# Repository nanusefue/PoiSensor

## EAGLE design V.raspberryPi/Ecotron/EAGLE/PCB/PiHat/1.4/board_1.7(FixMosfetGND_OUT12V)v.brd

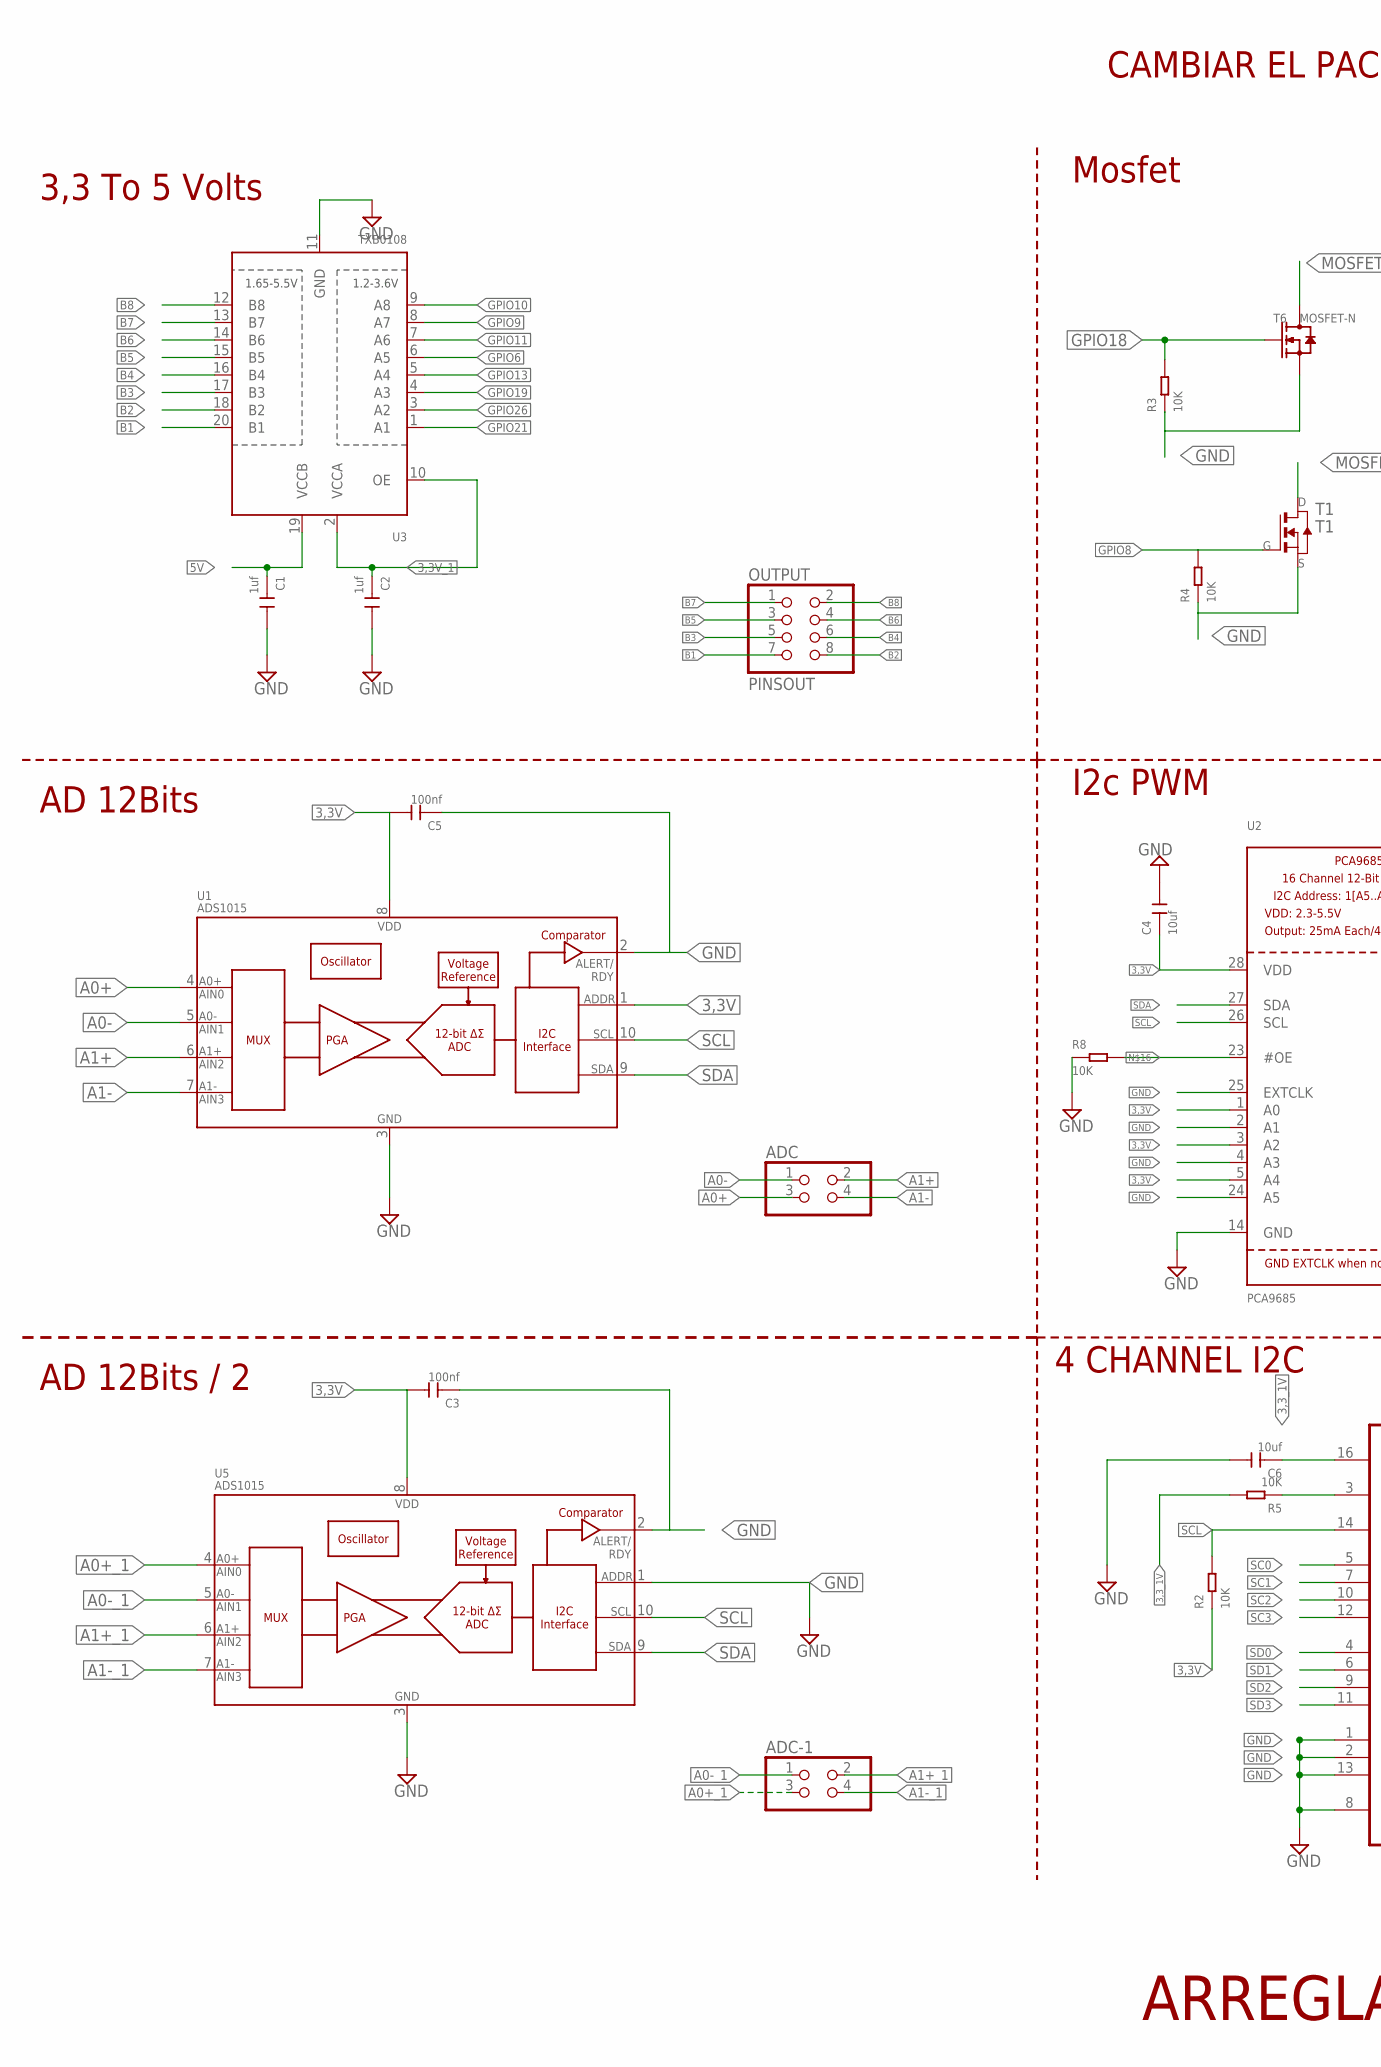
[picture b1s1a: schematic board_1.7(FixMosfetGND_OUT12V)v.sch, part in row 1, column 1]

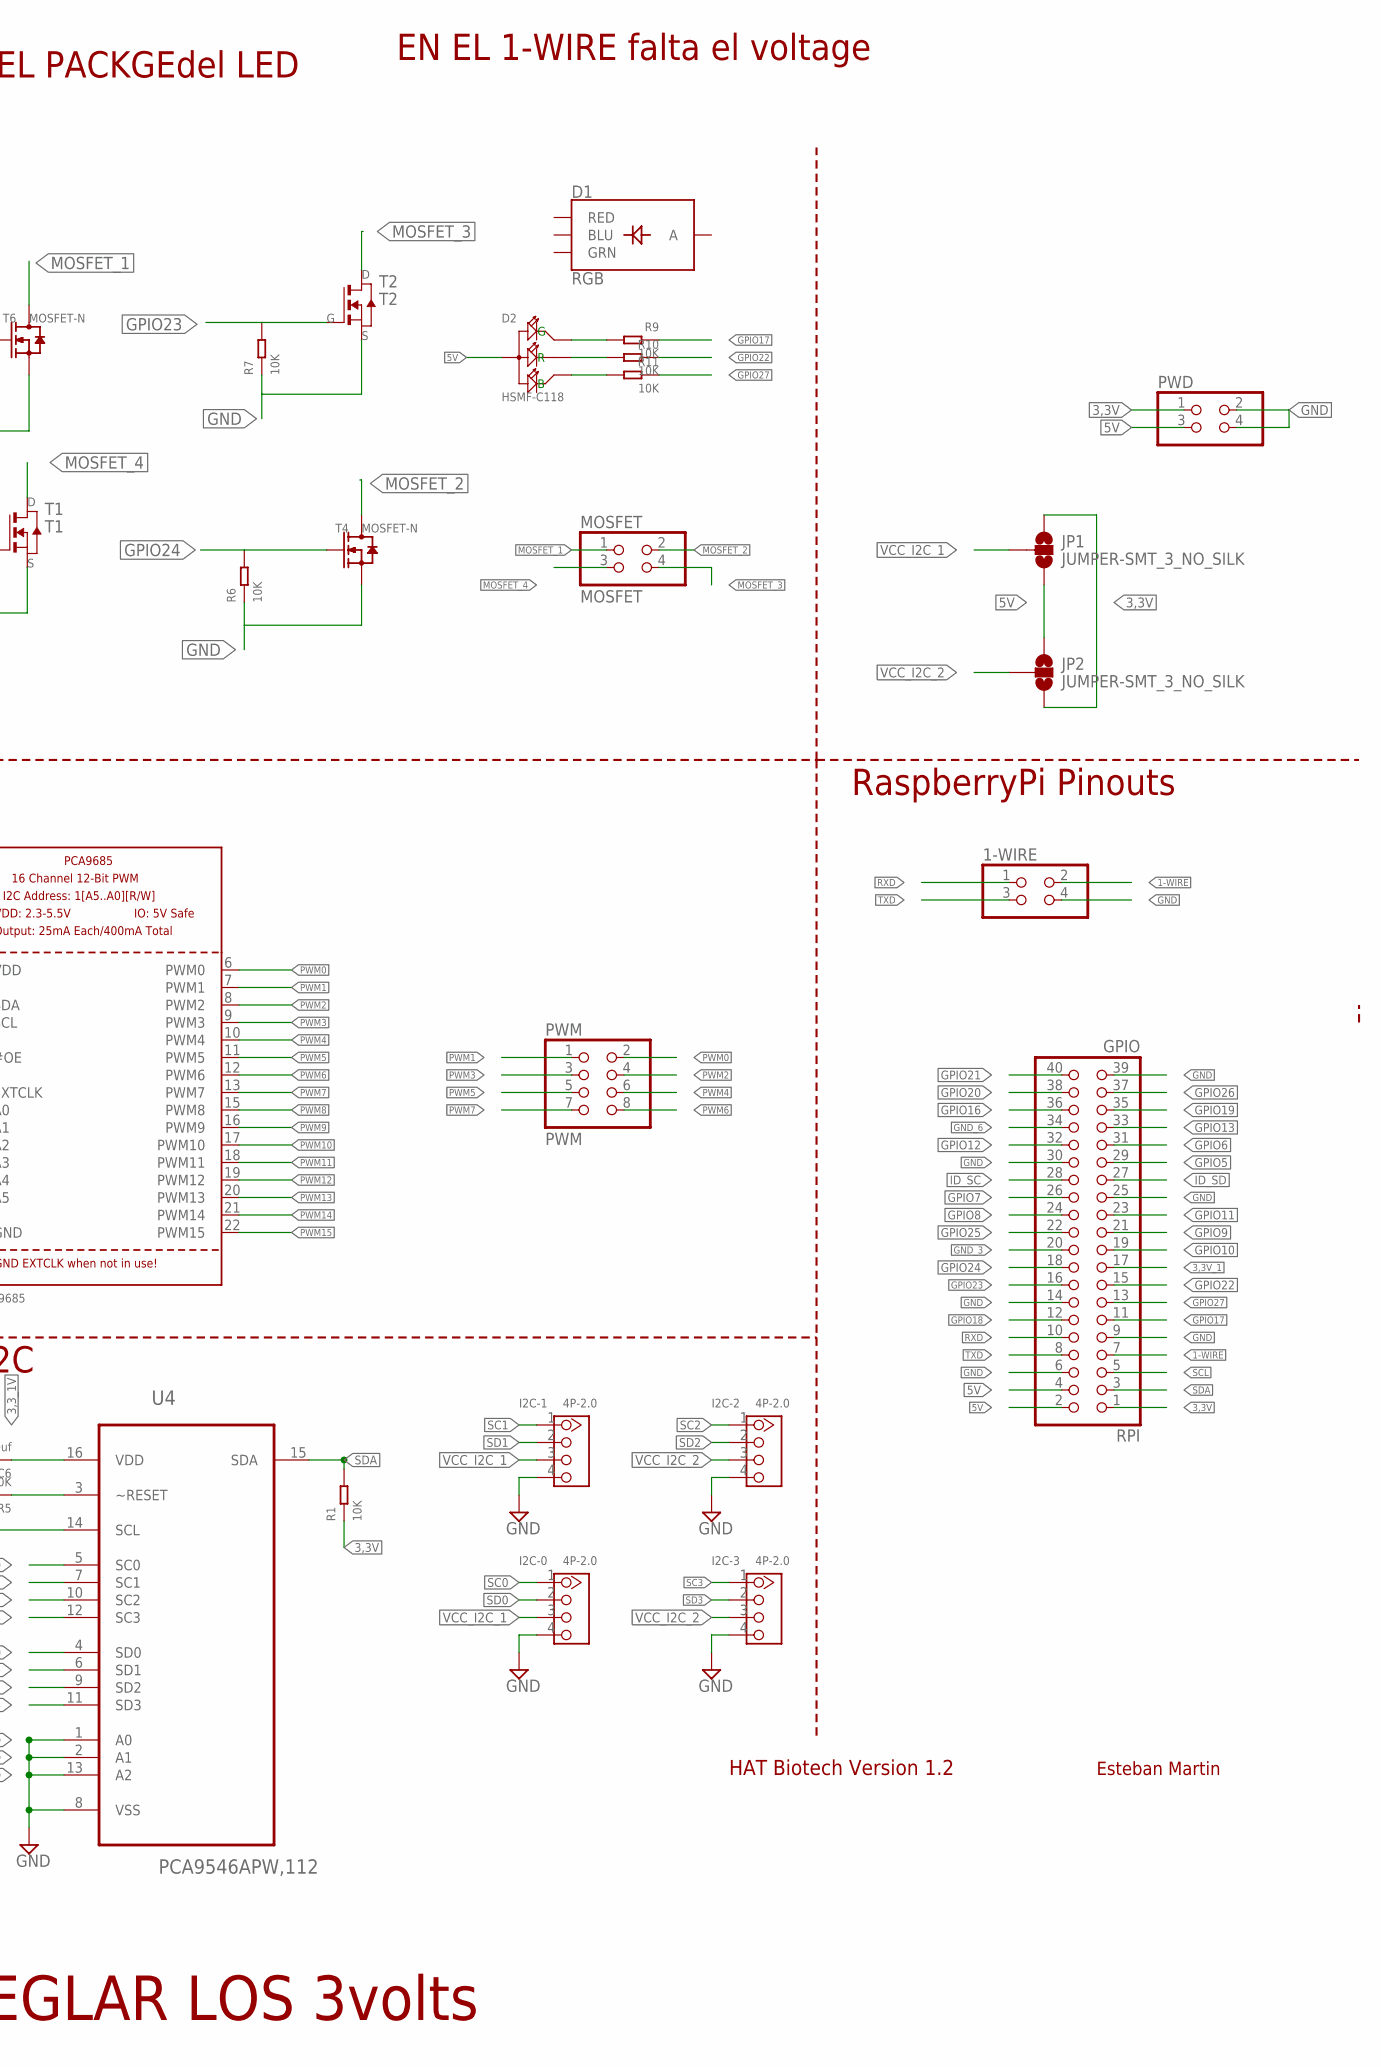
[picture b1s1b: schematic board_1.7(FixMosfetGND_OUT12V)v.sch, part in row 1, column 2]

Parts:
1-WIRE: PINHD-2X2; 2X02
ADC: PINHD-2X2; 2X02
ADC-1: PINHD-2X2; 2X02
C1, C2: 1uf; C0805
C3, C5: 100nf; C0805
C4, C6: 10uf; C0805
D1: RGB; P-LCC-4-3
D2: HSMF-C118; LED4-SMD-1210
I2C-0, I2C-1, I2C-2, I2C-3: 4P-2.0; HW4-2.0
JP1, JP2: JUMPER-SMT_3_NO_SILK; SMT-JUMPER_3_NO_SILK
MOSFET: MOSFET; 2X02
OUTPUT: PINSOUT; 2X04
PWD: PINHD-2X2; 2X02
PWM: PWM; 2X04
R1, R2, R3, R4, R5, R6, R7, R8, R9, R10, R11: 10K; R0805
RPI: GPIO; 2X20
T1: T1; TO252
T2: T2; TO252
T4, T6: MOSFET-N; SOT-23
U1, U5: ADS1015; MSOP10
U2: PCA9685; TSSOP28
U3: TXB0108; TSSOP20
U4: PCA9546APW,112; SOP65P640X110-16N

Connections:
1-WIRE: 1-WIRE.2, RPI.7
3,3V: C3.2, C4.1, C5.2, JP1.1, JP2.3, PWD.1, R1.1, R2.1, RPI.1, U1.1 (ADDR), U1.8 (VDD), U2.1 (A0), U2.3 (A2), U2.5 (A4), U2.28 (VDD), U5.8 (VDD)
3,3V_1: C2.1, RPI.17, U3.2 (VCCA), U3.10 (OE)
3,3_1V: C6.1, R5.2, U4.16 (VDD)
5V: C1.1, D2.1 (+), JP1.3, JP2.1, PWD.3, RPI.2, RPI.4, U3.19 (VCCB)
A0+: ADC.3, U1.4 (AIN0)
A0+_1: ADC-1.3, U5.4 (AIN0)
A0-: ADC.1, U1.5 (AIN1)
A0-_1: ADC-1.1, U5.5 (AIN1)
A1+: ADC.2, U1.6 (AIN2)
A1+_1: ADC-1.2, U5.6 (AIN2)
A1-: ADC.4, U1.7 (AIN3)
A1-_1: ADC-1.4, U5.7 (AIN3)
B1: OUTPUT.7, U3.20 (B1)
B2: OUTPUT.8, U3.18 (B2)
B3: OUTPUT.5, U3.17 (B3)
B4: OUTPUT.6, U3.16 (B4)
B5: OUTPUT.3, U3.15 (B5)
B6: OUTPUT.4, U3.14 (B6)
B7: OUTPUT.1, U3.13 (B7)
B8: OUTPUT.2, U3.12 (B8)
GND: 1-WIRE.4, C1.2, C2.2, C3.1, C4.2, C5.1, C6.2, I2C-0.4, I2C-1.4, I2C-2.4, I2C-3.4, PWD.2, PWD.4, R3.1, R4.1, R6.1, R7.1, R8.1, RPI.6, RPI.9, RPI.14, RPI.25, RPI.30, RPI.39, T1.2 (S), T2.2 (S), T4.2 (S), T6.2 (S), U1.2 (ALERT/RDY), U1.3 (VSS), U2.2 (A1), U2.4 (A3), U2.14 (GND), U2.24 (A5), U2.25 (EXTCLK), U3.11 (GND), U4.1 (A0), U4.2 (A1), U4.8 (VSS), U4.13 (A2), U5.1 (ADDR), U5.2 (ALERT/RDY), U5.3 (VSS)
GND_3: RPI.20
GND_6: RPI.34
GPIO5: RPI.29
GPIO6: RPI.31, U3.6 (A5)
GPIO7: RPI.26
GPIO8: R4.2, RPI.24, T1.1 (G)
GPIO9: RPI.21, U3.8 (A7)
GPIO10: RPI.19, U3.9 (A8)
GPIO11: RPI.23, U3.7 (A6)
GPIO12: RPI.32
GPIO13: RPI.33, U3.5 (A4)
GPIO16: RPI.36
GPIO17: R9.1, RPI.11
GPIO18: R3.2, RPI.12, T6.1 (G)
GPIO19: RPI.35, U3.4 (A3)
GPIO20: RPI.38
GPIO21: RPI.40, U3.1 (A1)
GPIO22: R10.1, RPI.15
GPIO23: R7.2, RPI.16, T2.1 (G)
GPIO24: R6.2, RPI.18, T4.1 (G)
GPIO25: RPI.22
GPIO26: RPI.37, U3.3 (A2)
GPIO27: R11.1, RPI.13
ID_SC: RPI.28
ID_SD: RPI.27
MOSFET_1: MOSFET.1, T6.3 (D)
MOSFET_2: MOSFET.2, T4.3 (D)
MOSFET_3: MOSFET.4, T2.3 (D)
MOSFET_4: MOSFET.3, T1.3 (D)
unnamed: D2.3 (G), R9.2
unnamed: D2.2 (R), R10.2
unnamed: D2.4 (B), R11.2
unnamed: R5.1, U4.3 (~RESET)
unnamed: R8.2, U2.23 (#OE)
PWM0: PWM.2, U2.6 (PWM0)
PWM1: PWM.1, U2.7 (PWM1)
PWM2: PWM.4, U2.8 (PWM2)
PWM3: PWM.3, U2.9 (PWM3)
PWM4: PWM.6, U2.10 (PWM4)
PWM5: PWM.5, U2.11 (PWM5)
PWM6: PWM.8, U2.12 (PWM6)
PWM7: PWM.7, U2.13 (PWM7)
PWM8: U2.15 (PWM8)
PWM9: U2.16 (PWM9)
PWM10: U2.17 (PWM10)
PWM11: U2.18 (PWM11)
PWM12: U2.19 (PWM12)
PWM13: U2.20 (PWM13)
PWM14: U2.21 (PWM14)
PWM15: U2.22 (PWM15)
RXD: 1-WIRE.1, RPI.10
SC0: I2C-0.1, U4.5 (SC0)
SC1: I2C-1.1, U4.7 (SC1)
SC2: I2C-2.1, U4.10 (SC2)
SC3: I2C-3.1, U4.12 (SC3)
SCL: R2.2, RPI.5, U1.10 (SCL), U2.26 (SCL), U4.14 (SCL), U5.10 (SCL)
SD0: I2C-0.2, U4.4 (SD0)
SD1: I2C-1.2, U4.6 (SD1)
SD2: I2C-2.2, U4.9 (SD2)
SD3: I2C-3.2, U4.11 (SD3)
SDA: R1.2, RPI.3, U1.9 (SDA), U2.27 (SDA), U4.15 (SDA), U5.9 (SDA)
TXD: 1-WIRE.3, RPI.8
VCC_I2C_1: I2C-0.3, I2C-1.3, JP1.2
VCC_I2C_2: I2C-2.3, I2C-3.3, JP2.2

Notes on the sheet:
AD 12Bits
3,3 To 5 Volts
Mosfet
RaspberryPi Pinouts
I2c PWM
HAT Biotech Version 1.2
Esteban Martin
4 CHANNEL I2C
AD 12Bits / 2
ARREGLAR LOS 3volts
CAMBIAR EL PACKGEdel LED
EN EL 1-WIRE falta el voltage

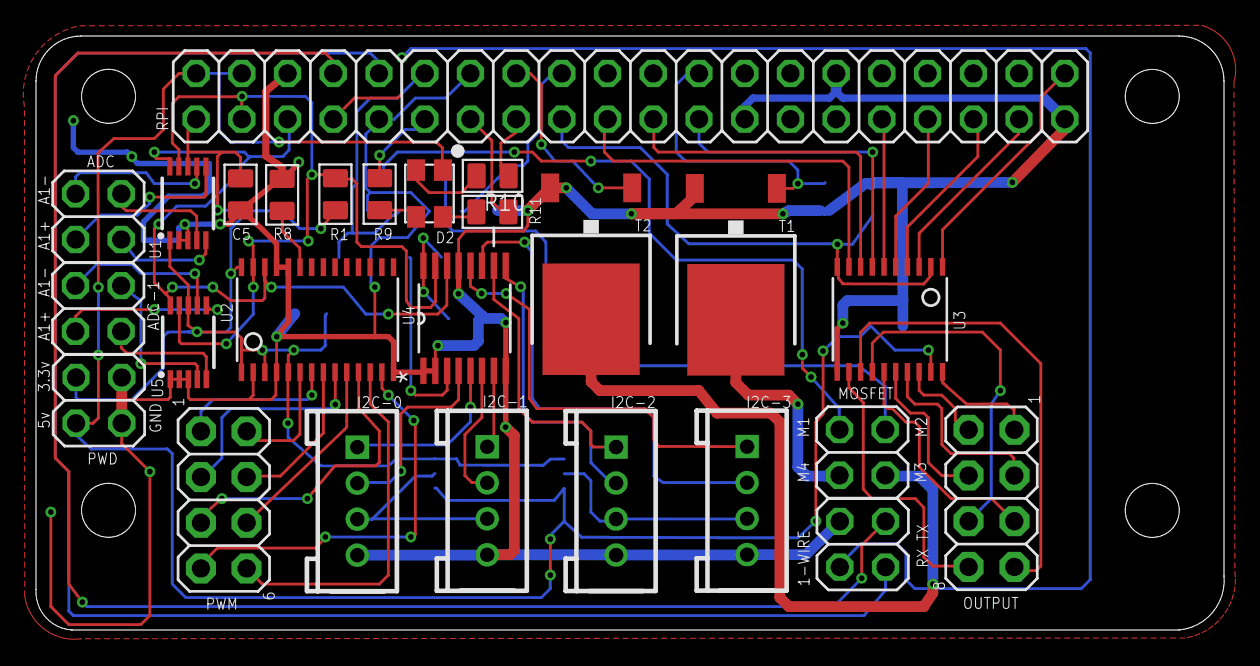
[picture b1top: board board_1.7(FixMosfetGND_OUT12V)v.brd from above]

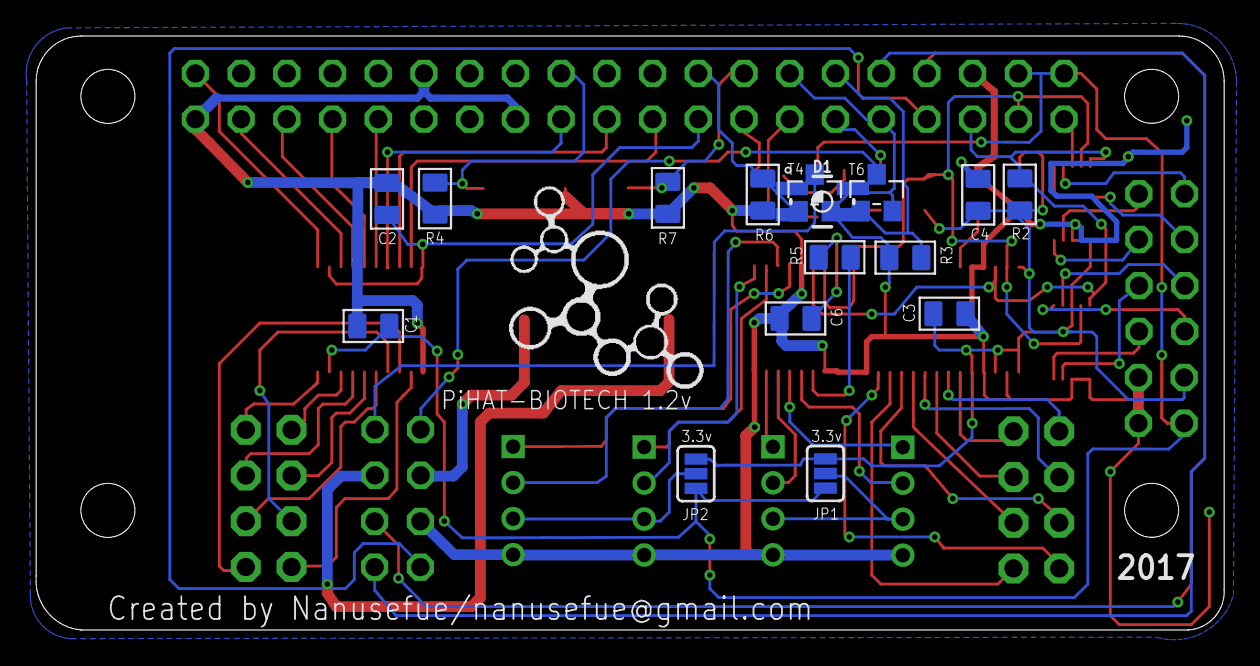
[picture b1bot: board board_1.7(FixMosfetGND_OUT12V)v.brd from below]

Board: 2 copper layers, 66.0 x 33.0 mm, 42 parts (16 on the bottom side), 68 nets.

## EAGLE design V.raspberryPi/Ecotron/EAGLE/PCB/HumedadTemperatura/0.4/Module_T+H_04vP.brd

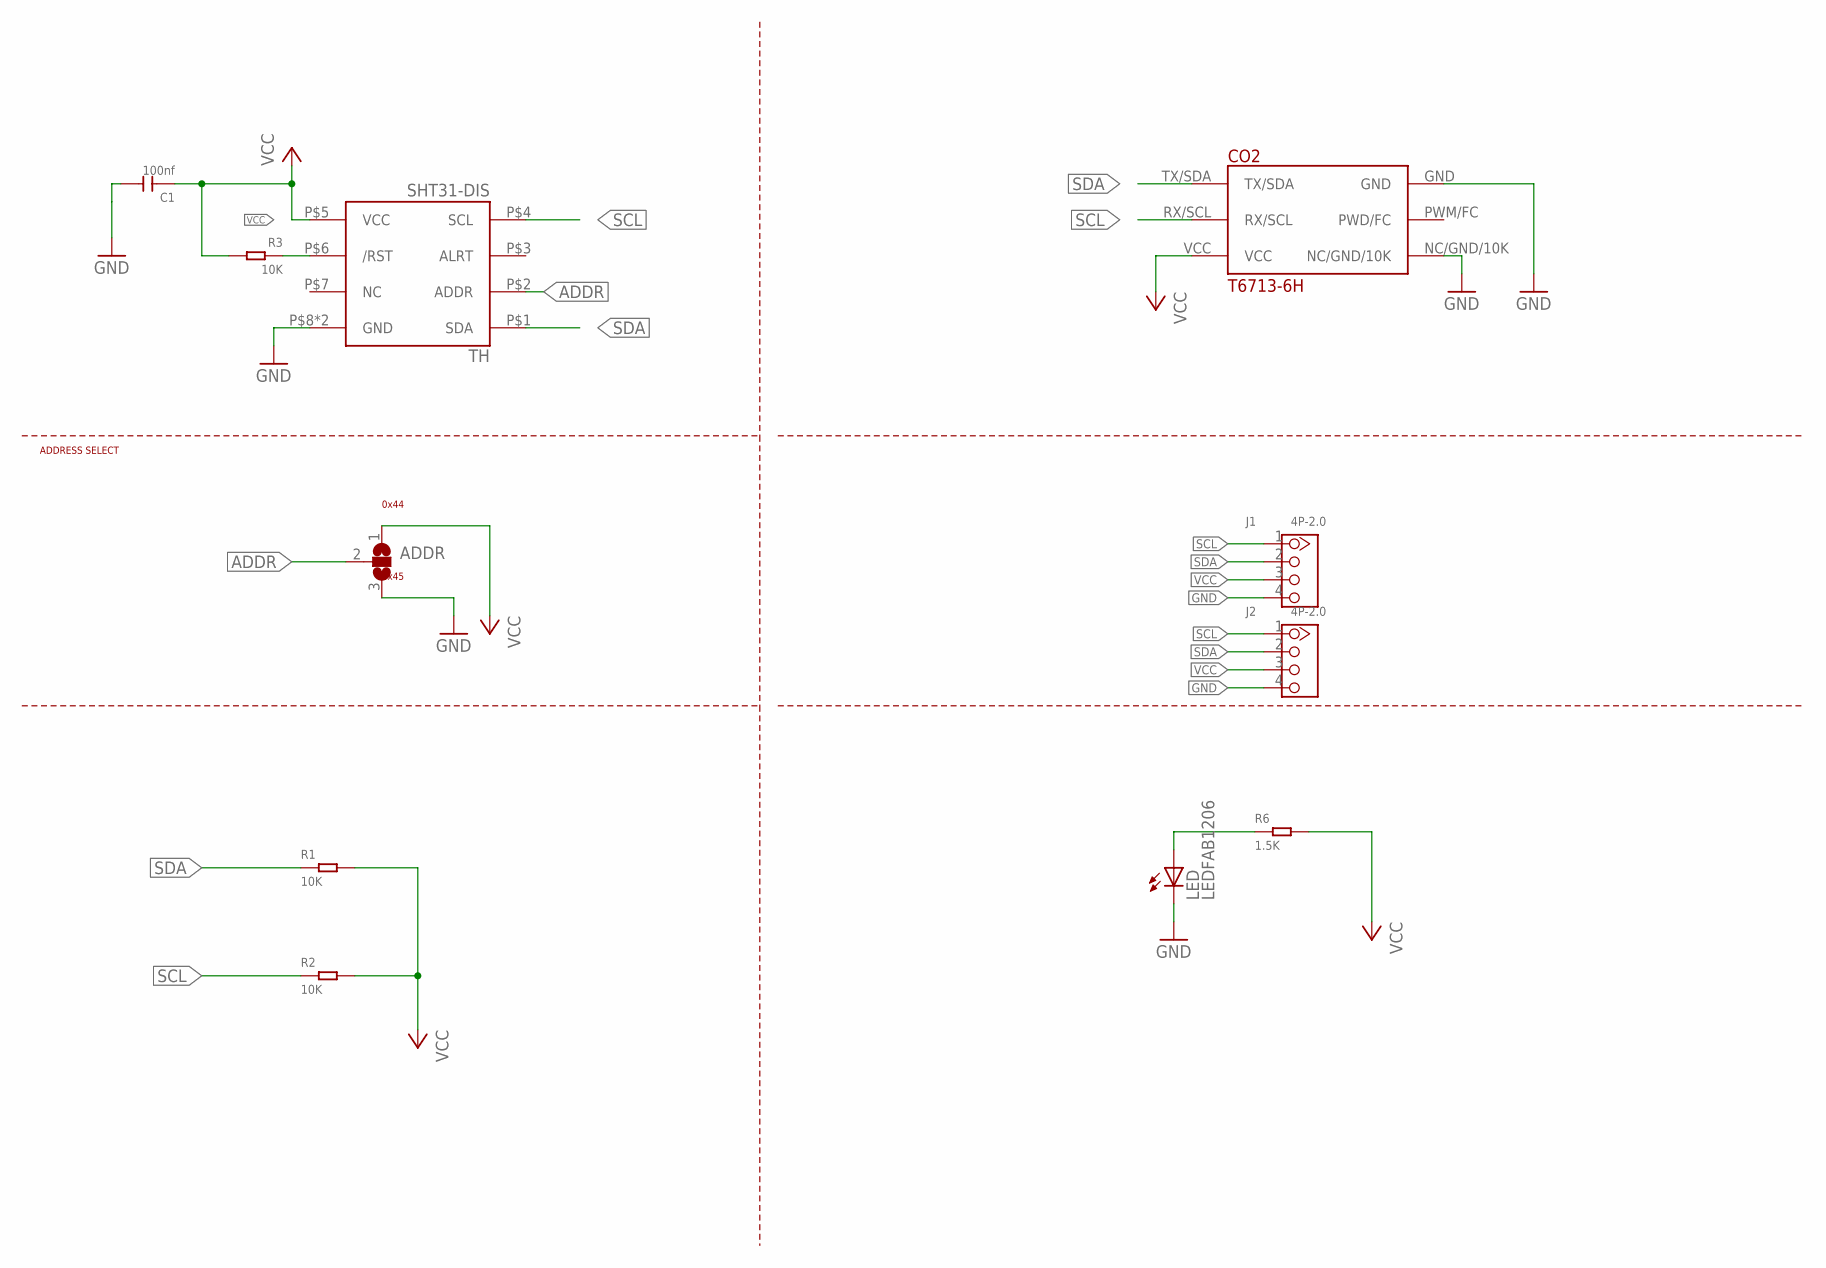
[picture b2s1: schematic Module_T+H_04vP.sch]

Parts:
ADDR: SJ2W; SJ_2
C1: 100nf; C0805
CO2: T6713-6H; PINS
J1, J2: 4P-2.0; HW4-2.0
LED: LEDFAB1206; LED1206FAB
R1, R2, R3: 10K; R0805
R6: 1.5K; R0805
TH: SHT31-DIS; SHT3X

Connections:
ADDR: ADDR.2, TH.P$2 (ADDR)
GND: ADDR.3, C1.2, CO2.GND, CO2.NC/GND/10K, J1.4, J2.4, LED.2 (C), TH.P$8 (GND), TH.PAD (GND)
unnamed: LED.1 (A), R6.1
RST: R3.1, TH.P$6 (/RST)
SCL: CO2.RX/SCL, J1.1, J2.1, R2.1, TH.P$4 (SCL)
SDA: CO2.TX/SDA, J1.2, J2.2, R1.1, TH.P$1 (SDA)
VCC: ADDR.1, C1.1, CO2.VCC, J1.3, J2.3, R1.2, R2.2, R3.2, R6.2, TH.P$5 (VCC)

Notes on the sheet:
ADDRESS SELECT
0x44
0x45

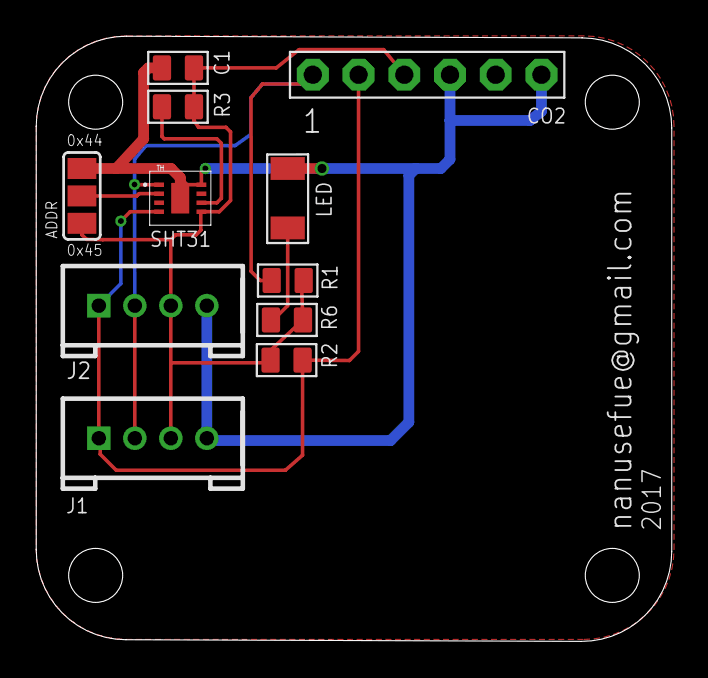
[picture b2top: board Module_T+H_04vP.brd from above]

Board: 2 copper layers, 35.3 x 33.6 mm, 11 parts (0 on the bottom side), 7 nets.

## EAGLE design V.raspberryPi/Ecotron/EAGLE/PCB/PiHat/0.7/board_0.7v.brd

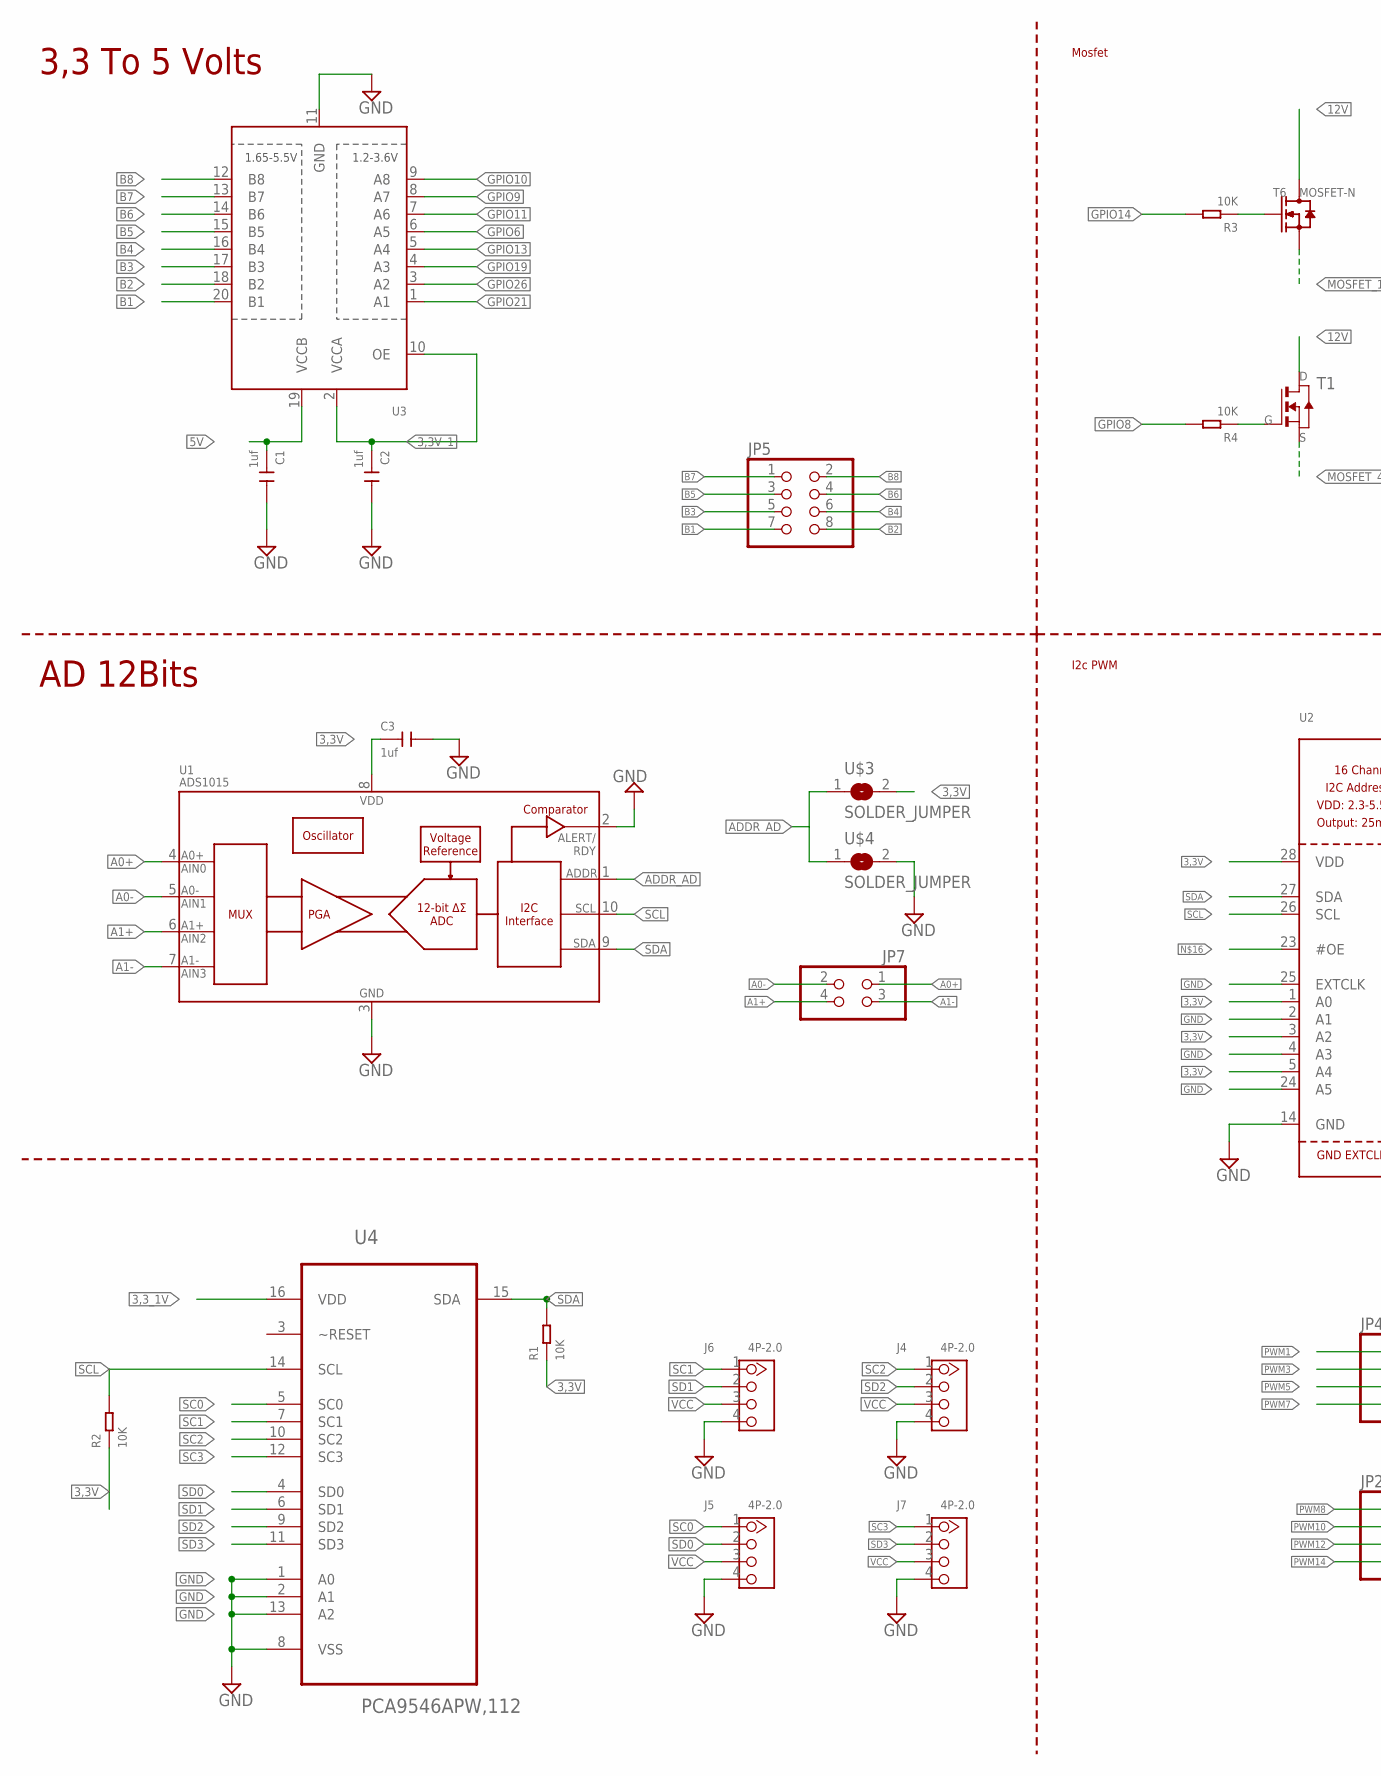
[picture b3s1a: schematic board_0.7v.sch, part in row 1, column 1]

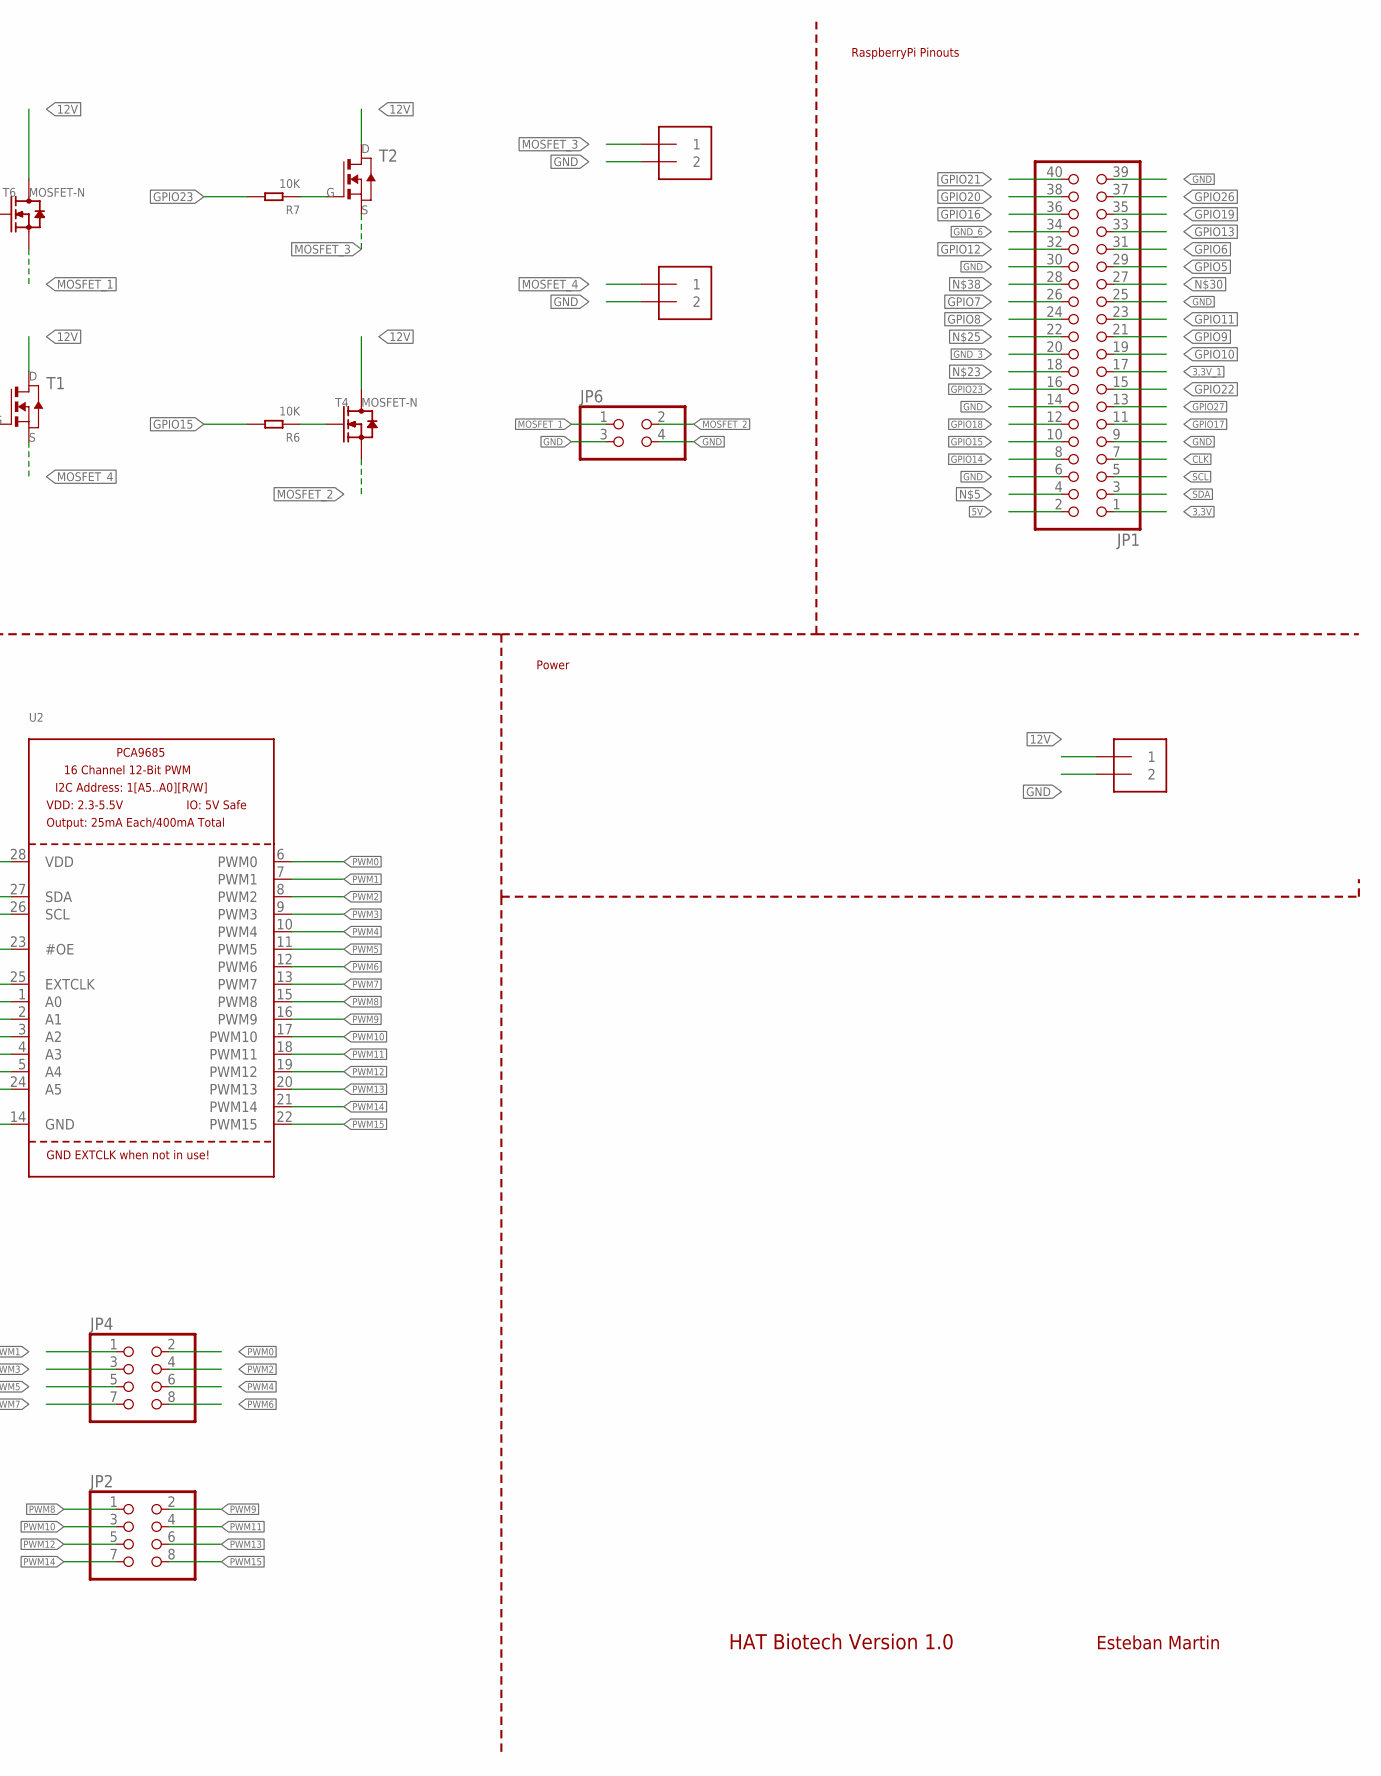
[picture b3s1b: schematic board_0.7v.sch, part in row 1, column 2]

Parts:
C1, C2, C3: 1uf; C0805
J1, J2, J3: 1X2-3.5MM
J4, J5, J6, J7: 4P-2.0; HW4-2.0
JP1: PINHD-2X20; 2X20
JP2, JP4, JP5: PINHD-2X4; 2X04
JP6, JP7: PINHD-2X2; 2X02
R1, R2, R3, R4, R6, R7: 10K; R0805
T1, T2: NMOSFETTO252; TO252
T4, T6: MOSFET-N; SOT-23
U1: ADS1015; MSOP10
U2: PCA9685; TSSOP28
U3: TXB0108PWR; TSSOP20
U4: PCA9546APW,112; SOP65P640X110-16N
U$3, U$4: SOLDER_JUMPER; SJFAB

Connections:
3,3V: C3.1, JP1.1, R1.1, R2.1, U1.8 (VDD), U2.1 (A0), U2.3 (A2), U2.5 (A4), U2.28 (VDD), U$3.2; also elsewhere on the board
3,3V_1: C2.1, JP1.17, U3.2 (VCCA), U3.10 (OE)
3,3_1V: U4.16 (VDD)
5V: C1.1, JP1.2, U3.19 (VCCB)
12V: J2.1, T1.3 (D), T2.3 (D), T4.3 (D), T6.3 (D)
A0+: JP7.1, U1.4 (AIN0)
A0-: JP7.2, U1.5 (AIN1)
A1+: JP7.4, U1.6 (AIN2)
A1-: JP7.3, U1.7 (AIN3)
ADDR_AD: U1.1 (ADDR), U$3.1, U$4.1; also elsewhere on the board
B1: JP5.7, U3.20 (B1)
B2: JP5.8, U3.18 (B2)
B3: JP5.5, U3.17 (B3)
B4: JP5.6, U3.16 (B4)
B5: JP5.3, U3.15 (B5)
B6: JP5.4, U3.14 (B6)
B7: JP5.1, U3.13 (B7)
B8: JP5.2, U3.12 (B8)
CLK: JP1.7
GND: C1.2, C2.2, C3.2, J1.2, J2.2, J3.2, J4.4, J5.4, J6.4, J7.4, JP1.6, JP1.9, JP1.14, JP1.25, JP1.30, JP1.39, JP6.3, JP6.4, U1.2 (ALERT/RDY), U1.3 (VSS), U2.2 (A1), U2.4 (A3), U2.14 (GND), U2.24 (A5), U2.25 (EXTCLK), U3.11 (GND), U4.1 (A0), U4.2 (A1), U4.8 (VSS), U4.13 (A2), U$4.2; also elsewhere on the board
GND_3: JP1.20
GND_6: JP1.34
GPIO5: JP1.29
GPIO6: JP1.31, U3.6 (A5)
GPIO7: JP1.26
GPIO8: JP1.24, R4.2
GPIO9: JP1.21, U3.8 (A7)
GPIO10: JP1.19, U3.9 (A8)
GPIO11: JP1.23, U3.7 (A6)
GPIO12: JP1.32
GPIO13: JP1.33, U3.5 (A4)
GPIO14: JP1.8, R3.2
GPIO15: JP1.10, R6.2
GPIO16: JP1.36
GPIO17: JP1.11
GPIO18: JP1.12
GPIO19: JP1.35, U3.4 (A3)
GPIO20: JP1.38
GPIO21: JP1.40, U3.1 (A1)
GPIO22: JP1.15
GPIO23: JP1.16, R7.2
GPIO26: JP1.37, U3.3 (A2)
GPIO27: JP1.13
MOSFET_1: JP6.1, T6.2 (S)
MOSFET_2: JP6.2, T4.2 (S)
MOSFET_3: J1.1, T2.2 (S)
MOSFET_4: J3.1, T1.2 (S)
unnamed: R3.1, T6.1 (G)
unnamed: R4.1, T1.1 (G)
unnamed: R6.1, T4.1 (G)
unnamed: R7.1, T2.1 (G)
PWM0: JP4.2, U2.6 (PWM0)
PWM1: JP4.1, U2.7 (PWM1)
PWM2: JP4.4, U2.8 (PWM2)
PWM3: JP4.3, U2.9 (PWM3)
PWM4: JP4.6, U2.10 (PWM4)
PWM5: JP4.5, U2.11 (PWM5)
PWM6: JP4.8, U2.12 (PWM6)
PWM7: JP4.7, U2.13 (PWM7)
PWM8: JP2.1, U2.15 (PWM8)
PWM9: JP2.2, U2.16 (PWM9)
PWM10: JP2.3, U2.17 (PWM10)
PWM11: JP2.4, U2.18 (PWM11)
PWM12: JP2.5, U2.19 (PWM12)
PWM13: JP2.6, U2.20 (PWM13)
PWM14: JP2.7, U2.21 (PWM14)
PWM15: JP2.8, U2.22 (PWM15)
SC0: J5.1, U4.5 (SC0)
SC1: J6.1, U4.7 (SC1)
SC2: J4.1, U4.10 (SC2)
SC3: J7.1, U4.12 (SC3)
SCL: JP1.5, R2.2, U1.10 (SCL), U2.26 (SCL), U4.14 (SCL)
SD0: J5.2, U4.4 (SD0)
SD1: J6.2, U4.6 (SD1)
SD2: J4.2, U4.9 (SD2)
SD3: J7.2, U4.11 (SD3)
SDA: JP1.3, R1.2, U1.9 (SDA), U2.27 (SDA), U4.15 (SDA)
VCC: J4.3, J5.3, J6.3, J7.3

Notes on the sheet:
AD 12Bits
3,3 To 5 Volts
Mosfet
RaspberryPi Pinouts
I2c PWM
Power
HAT Biotech Version 1.0
Esteban Martin

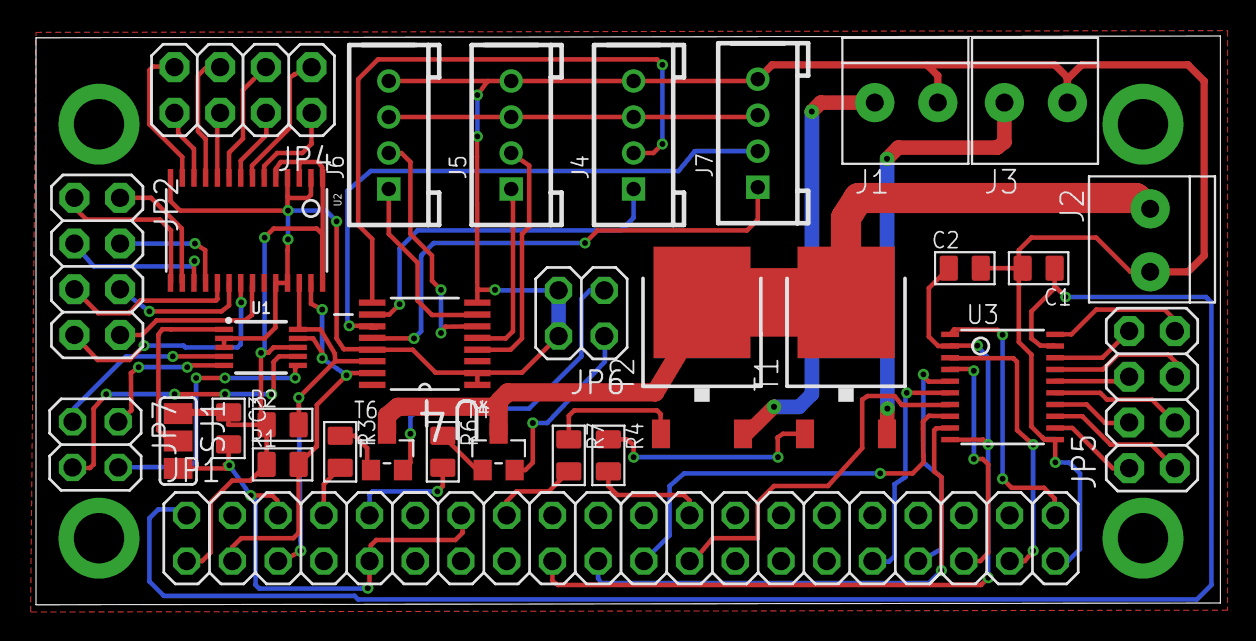
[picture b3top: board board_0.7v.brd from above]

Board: 2 copper layers, 65.8 x 31.6 mm, 31 parts (0 on the bottom side), 65 nets.

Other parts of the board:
SJ1: SJ_2

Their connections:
3,3V: SJ1.1; also elsewhere on the board
ADDR_AD: SJ1.2; also elsewhere on the board
GND: SJ1.3; also elsewhere on the board

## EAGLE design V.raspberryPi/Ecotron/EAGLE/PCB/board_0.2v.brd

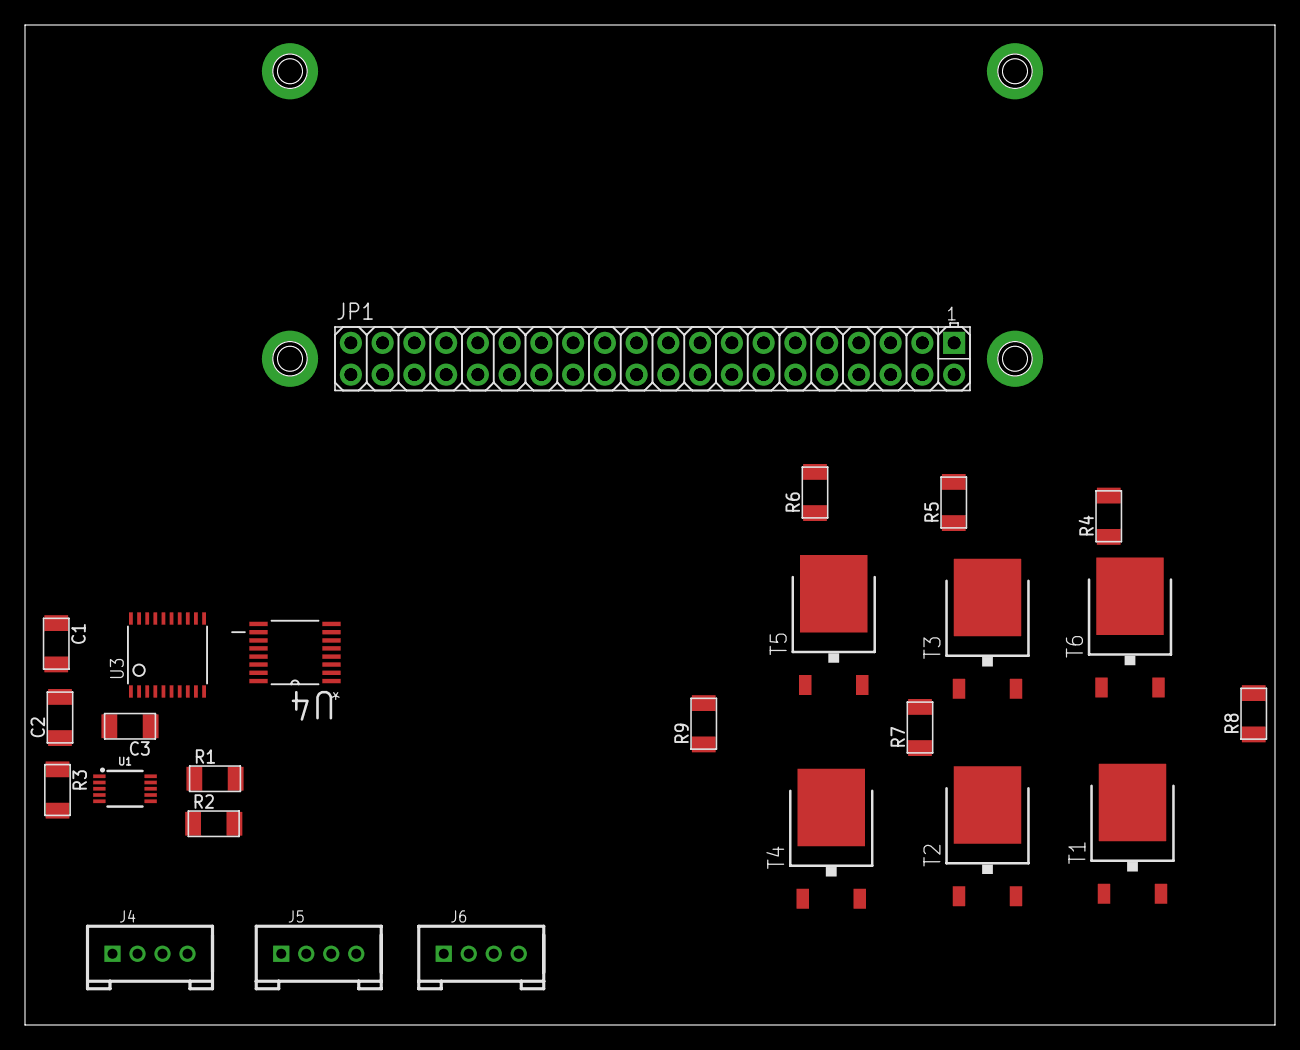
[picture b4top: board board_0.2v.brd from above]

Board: 2 copper layers, 100.0 x 80.0 mm, 26 parts (0 on the bottom side), 14 nets, no tracks yet.

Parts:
C1, C2, C3: CAP-US1206FAB; C1206FAB
J4, J5, J6: 4P-2.0; HW4-2.0
JP1: 2X20
R1, R2, R3, R4, R5, R6, R7, R8, R9: R1206FAB
T1, T2, T3, T4, T5, T6: TO252
U1: ADS1015; MSOP10
U3: TSSOP20
U4: PCA9546APW,112; SOP65P640X110-16N
U$1: RPI-ZERO; RASPBERRYPI_BASTELSTUBE_V13_RASPI_BOARD_B+_FULL

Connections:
GND: C1.2, C2.2, C3.2, J4.4, J5.4, J6.4, JP1.6, U1.3, U3.11, U4.8
unnamed: C3.1, U1.8
unnamed: C1.1, U3.19
unnamed: C2.1, U3.2
unnamed: R7.1, T2.1
unnamed: R1.1, U1.10
unnamed: R2.1, U1.9
unnamed: R1.2, R2.2
unnamed: R3.1, U1.1
unnamed: R6.1, T5.1
unnamed: R8.1, T1.1
unnamed: R9.1, T4.1
unnamed: R5.1, T3.1
unnamed: R4.1, T6.1

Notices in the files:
parts and their libraries:
SparkFun-IC-Conversion: Licensing: Creative Commons ShareAlike 4.0 International - https://creativecommons.org/licenses/by-sa/4.0
